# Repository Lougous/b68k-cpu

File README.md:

# Overview

This is a single board computer based on Motorola 68000. It features:
* 512kiB to 8MiB DRAM (SIMM 30 pins x2)
* basic memory protection / paging
* 8bits expansion bus with 4 slots
* PS/2 keyboard and mouse support
* serial link (TTL)
* boot with serial bootstrap or user flash

Some pictures [here](/doc).

The block diagram below depicts the board architecture:

## Board glue logic

Most board glue logic is implemented with an Altera EPM7128S CPLD. This part is obsolete but modern replacement exists with ~~Actel~~ ~~Microsemi~~ Microchip ATF1508AS (never tested though). The CPLD implements:
* DRAM address multiplexing
* DRAM refresh
* basic memory management: base address translation and inbound check with power of two alignment constraints
* 8-bits expansion bus access, for 8-bits wide or 16-bits wide memory cycle from the 68000
* first stage boot procedure, by copying during reset the 512 first bytes from the flash memory (see MFP chip description below) at address 000000h in DRAM. 

Expansion bus also uses a few discrete logic (74245 buffers and 74138 address decoder).

An additional 74148 encodes interrupt sources to CPU IPL0/1/2.

### memory management

The CPLD provides very basic memory management capabilities, for user mode accesses only (FC2 set to 0). It relies on two value set with four registers. These registers are write only, 16-bits, but only the upper bit 15:8 are used.

| register    | address | description             |
|:-----------:|:-------:|:------------------------|
| MMU_BASE_LO | FE0000h | base address bits 19:12 |
| MMU_BASE_HI | FE0002h | base address bits 22:20 |
| MMU_MASK_LO | FE0004h | address mask bits 19:12 |
| MMU_MASK_HI | FE0006h | address mask bits 21:20 |

Any user address is and'ed with MMU_MASK then or'ed with MMU_BASE. It results in a memory area allocated to a user program with a power of two size, with a base address aligned to its own size. Any user access that targets an address above the allocated size ends with a bus error.

### interrupt management

The autovectored interrupt scheme is used (VPA# assertion). To save pins on the CPLD the FC0 and FC1 are not available to identify an interrupt acknowledge cycle, so any read cycle at FFFFFFh with FC2 set to 1 is considered as such.

### 8-bits expansion bus

This bus provides access to 5 peripherals:
* 4 available through dedicated connectors (2x10 female pin headers)
* 1 embeded to the board: the MFP

It provides for each peripheral up to 128kiB aperture into CPU memory space.

The table below lists the signals on this bus as seen for each slot.

| signal  | type              | shared  | description          |
|:-------:|:-----------------:|:-------:|:--------------------:|
| RST#    | input             | yes     | system reset         |
| CE#     | input             | no      | access enable        |
| ACK#    | open drain output | yes     | access acknowledge   |
| WE#     | input             | yes     | write enable         |
| ALE#    | input             | yes     | address latch enable |
| IRQ#    | open drain output | option  | interrupt request    |
| A0      | input             | yes     | address bit 0        |
| AD[7:0] | bidir             | yes     | address / data       |

#### single access cycles

This is how translates a byte access from the 68000 (UDS# or LDS# alone)

note: peripherals like the MFP ignore the address bits 16:1 and can ignore the ALE# signal.

#### multiple access cycles

This is how translates a 16-bits access from the 68000 (UDS# and LDS#)

### Bootstrap loading

Right after a reset, the CPLD starts by transfering 512 bytes of data from the MFP FLASH_DATA register into the first bytes of DRAM. Then the very first 68000 memory access (at 0000000h) is performed.

Because any software is to be much bigger than just 512-bytes, this chunk of code must itself include assembly instructions to copy the rest of the code - still accessing FLASH_DATA register.

The MFP contains two software images for the 68000:
* a serial bootstrap, loading from the serial interface the binary to jump in, that is enables by pressing 's' key on a keyboard plugged into the PS/2 port
* or an embedded binary to jump in.

To change the embedded binary, the MFP firmware must be recompiled and programmed (the 68000 binary is a constant data table within the microcontroller firmware).

## MFP (multifunction peripheral)

This is a software defined chip base on a PIC18F27K42 microcontroller. It provides:
* embedded flash with 2 software images for the 68000, selection by detecting pressed key at reset. 
* IOs/timer with dedicated low-priority interrupt: two PS/2 port, one serial link, 1 kHz RTC timer
* 250 Hz system timer with dedicated highest-priority interrupt
* hard/soft reset
* debug register (POST or so)

The MFP has only two memory locations accessible through the expansion bus: one to set the actual register to access, the other to read or write data from/to the register.

| register    | address | description             |
|:-----------:|:-------:|:------------------------|
| MFP_DATA    | F00000h | MFP register data |
| MFP_ADDRESS | F00001h | MFP register index |

### Register set

| register    | index   | description             |
|:-----------:|:-------:|:------------------------|
| FLASH_DATA  | 0       | boot flash data access. flash data pointer auto increments |
| TICKS       | 3       | 4-us ticks counter, 0-249 |
| UART_STS    | 4       | UART status<br>bit 7: TX ready<br>bit 1: RX FIFO overflow<br>bit 0: RX FIFO underflow |
| UART_DATA   | 5       | UART data in/out |
| POST        | 7       | POST code (debug) |
| PS2P0_STS   | 8       | PS/2 port 0 status<br>bit 0: data available |
| PS2P0_DATA  | 9       | PS/2 port 0 data |
| PS2P1_STS   | 10      | PS/2 port 1 status<br>bit 0: data available |
| PS2P1_DATA  | 11      | PS/2 port 1 data |
| SYSCFG      | 12      | system tick configuration<br>bit 0: enable timer interrupt<br>bit 5: set by bootstap loader to prevent flash to RAM boot transfer<br>bit 6: enable self immediate interrupt<br>bit 7: soft reset |
| SYSSTS      | 13      |  system tick status<br>bit 0: timer interrupt pending<br>bit 6: self immediate interrupt pending |
| IRQCFG      | 14      | interrupt controller configuration<br>bit 0: enable RTC interrupt<br>bit 1: enable PS/2 keyboard interrupt<br>bit 2: enable PS/2 mouse interrupt<br>bit 3: enable UART RX interrupt |
| IRQSTS      | 15      | interrupt controller status<br>bit 0: RTC interrupt pending<br>bit 1: PS/2 keyboard interrupt pending<br>bit 2: PS/2 mouse interrupt pending<br>bit 3: UART RX interrupt pending |

# Memory mapping

| memory range      | access | size   | memory area
|:-----------------:|:------:|:------:|:-----
| 000000h - 7FFFFFh | U/S    | 8MiB   | DRAM. memory address translation/mask/check for user mode only |
| 800000h - EFFFFFh | S	     | 7MiB   | DO NOT USE. mirrors F00000h - FFFFFFh                          |
| F00000h - F1FFFFh | S      | 128kiB | MFP registers. address bits 16:1 are ignored                   |
| F20000h - F3FFFFh | S      | 128kiB | expansion bus connector J9                                     |
| F40000h - F5FFFFh | S      | 128kiB | expansion bus connector J11                                    |
| F60000h - F7FFFFh | S      | 128kiB | DO NOT USE. reserved for expansion bus hardware implementation |
| F80000h - F9FFFFh | U*/S   | 128kiB | expansion bus connector J10. *: user access to be removed      |
| FA0000h - FBFFFFh | S      | 128kiB | DO NOT USE. unmapped, might be used for another peripheral slot |
| FC0000h - FDFFFFh | S      | 128kiB | expansion bus connector J8                                     |
| FE0000h - FFFFFFh | S      | 128kiB | restricted to PMMU register configuration                      |

# BOM

This table below is no spec, it just shows the parts that equip the board on my desk.

| Reference  | Part |
|:-----------------:|:------:|
| RN1 | not populated |
| U1 | MC68HC000FN20 |
| U2 | 74F138 |
| U3, U6, U7 | 74F245 |
| U4 | EPM7128SLC84-10 |
| U5 | PIC18F27K42SP |
| U8 | 74HC148 |
| X2 | 12-MHz |

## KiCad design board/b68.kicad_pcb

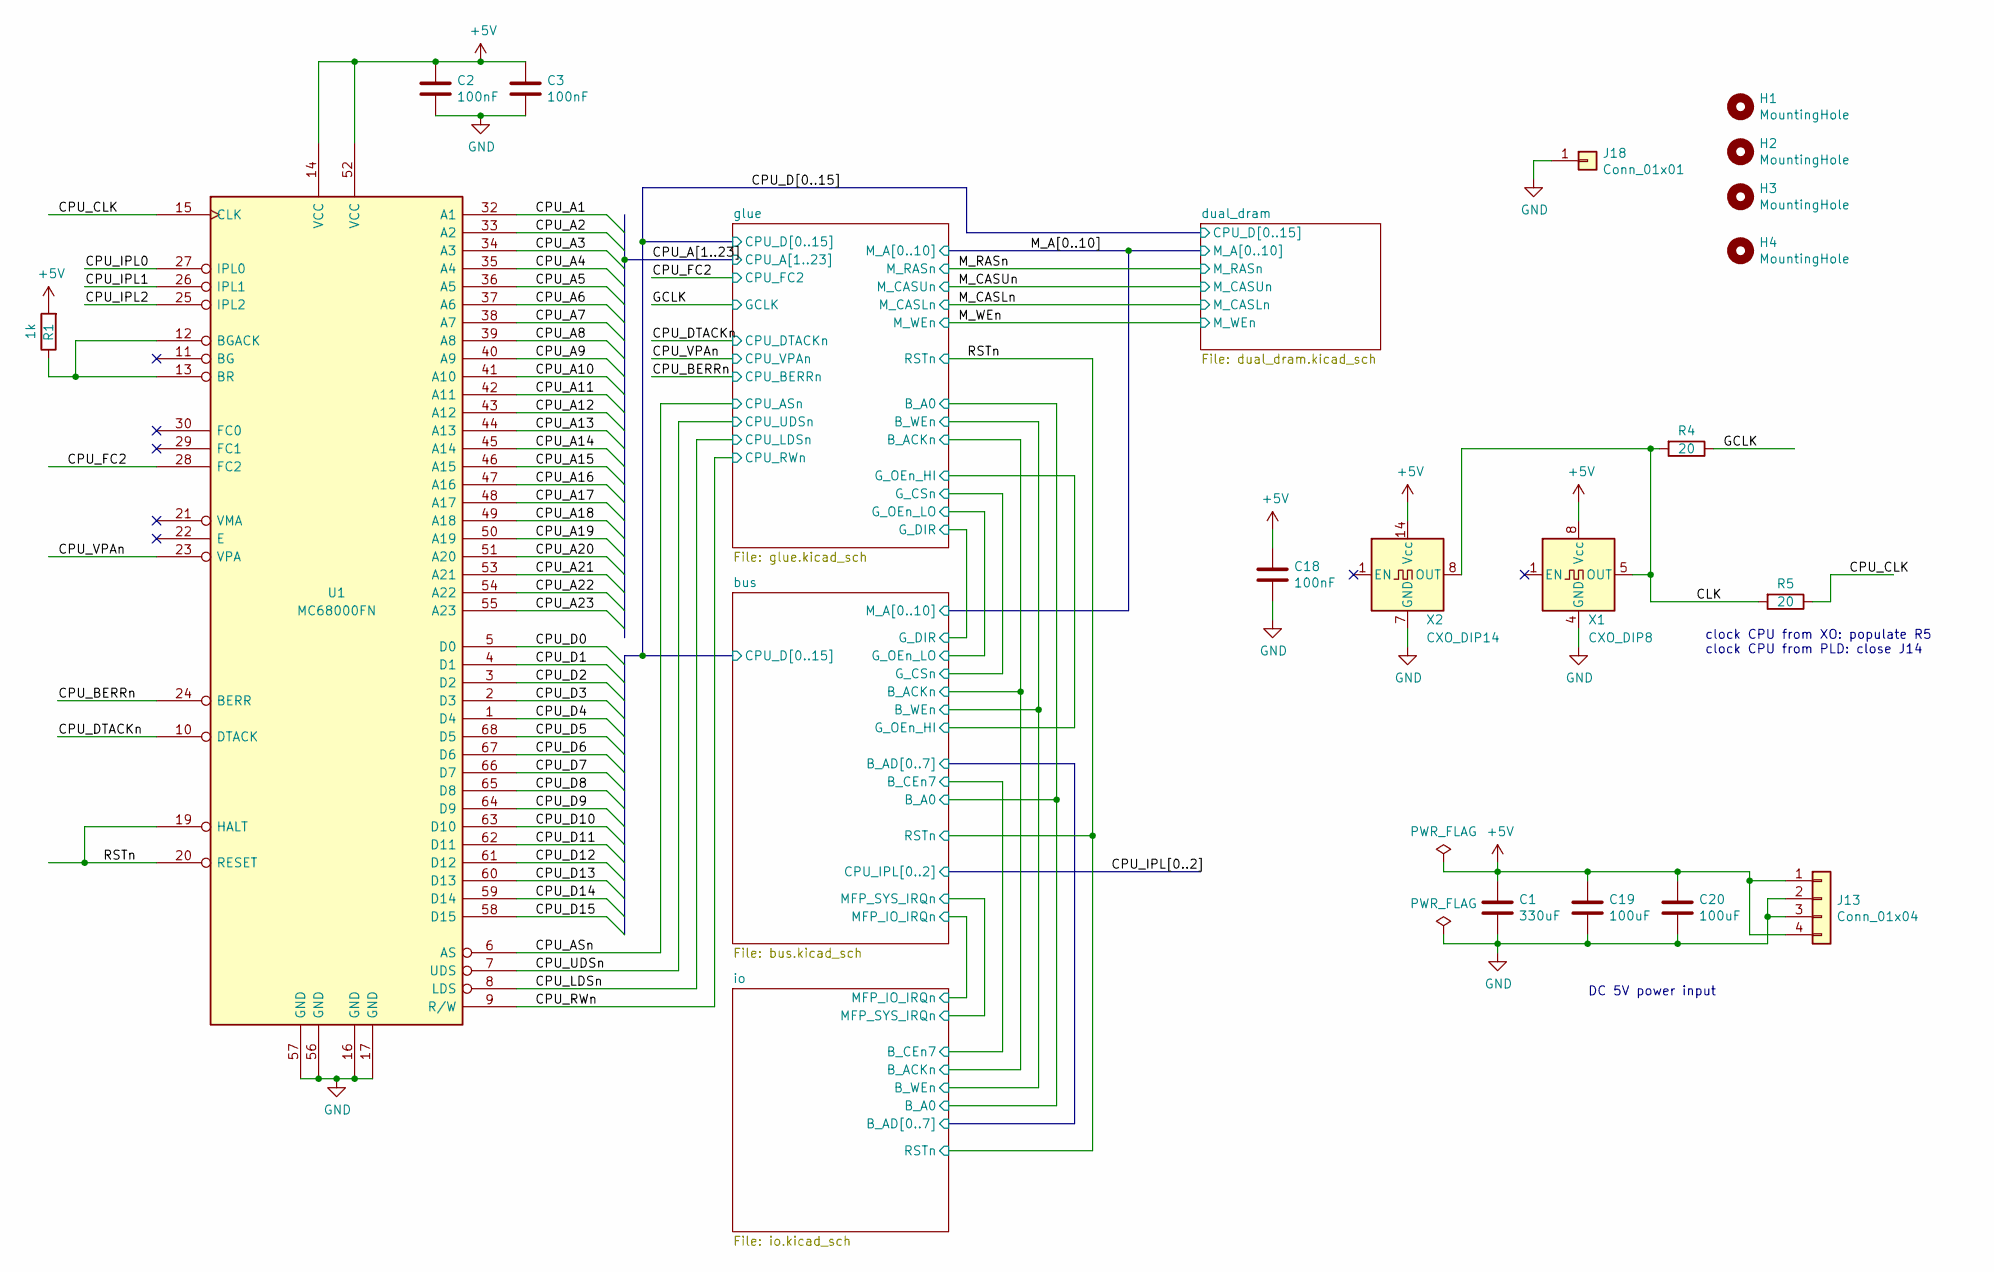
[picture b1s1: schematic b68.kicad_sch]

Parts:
C1: 330uF; CP_Radial_D8.0mm_P3.50mm
C2, C3, C18: 100nF; C_Disc_D4.3mm_W1.9mm_P5.00mm
C19, C20: 100uF; CP_Radial_D5.0mm_P2.50mm
H1, H2, H3, H4: MountingHole; MountingHole_2.7mm_M2.5_DIN965_Pad
J13: Conn_01x04; PinHeader_1x04_P2.54mm_Vertical
J18: Conn_01x01; PinHeader_1x01_P2.54mm_Vertical
R1: 1k; R_Axial_DIN0204_L3.6mm_D1.6mm_P7.62mm_Horizontal
R4, R5: 20; R_Axial_DIN0204_L3.6mm_D1.6mm_P7.62mm_Horizontal
U1: MC68000FN; PLCC-68_THT-Socket
X1: CXO_DIP8; Oscillator_DIP-8
X2: CXO_DIP14; Oscillator_DIP-14

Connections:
+5V: C1.1, C2.1, C3.1, C18.1, C19.1, C20.1, J13.1, J13.4, R1.2, U1.14 (VCC), U1.52 (VCC), X1.8 (Vcc), X2.14 (Vcc); also elsewhere on the board
/CLK: R4.2, R5.2, X1.5 (OUT), X2.8 (OUT)
/CPU_A1: U1.32 (A1); also elsewhere on the board
/CPU_A2: U1.33 (A2); also elsewhere on the board
/CPU_A3: U1.34 (A3); also elsewhere on the board
/CPU_A4: U1.35 (A4); also elsewhere on the board
/CPU_A5: U1.36 (A5); also elsewhere on the board
/CPU_A6: U1.37 (A6); also elsewhere on the board
/CPU_A7: U1.38 (A7); also elsewhere on the board
/CPU_A8: U1.39 (A8); also elsewhere on the board
/CPU_A9: U1.40 (A9); also elsewhere on the board
/CPU_A10: U1.41 (A10); also elsewhere on the board
/CPU_A11: U1.42 (A11); also elsewhere on the board
/CPU_A12: U1.43 (A12); also elsewhere on the board
/CPU_A13: U1.44 (A13); also elsewhere on the board
/CPU_A14: U1.45 (A14); also elsewhere on the board
/CPU_A15: U1.46 (A15); also elsewhere on the board
/CPU_A16: U1.47 (A16); also elsewhere on the board
/CPU_A17: U1.48 (A17); also elsewhere on the board
/CPU_A18: U1.49 (A18); also elsewhere on the board
/CPU_A19: U1.50 (A19); also elsewhere on the board
/CPU_A20: U1.51 (A20); also elsewhere on the board
/CPU_A21: U1.53 (A21); also elsewhere on the board
/CPU_A22: U1.54 (A22); also elsewhere on the board
/CPU_A23: U1.55 (A23); also elsewhere on the board
/CPU_ASn: U1.6 (AS); also elsewhere on the board
/CPU_BERRn: U1.24 (BERR); also elsewhere on the board
/CPU_CLK: R5.1, U1.15 (CLK)
/CPU_D0: U1.5 (D0); also elsewhere on the board
/CPU_D1: U1.4 (D1); also elsewhere on the board
/CPU_D2: U1.3 (D2); also elsewhere on the board
/CPU_D3: U1.2 (D3); also elsewhere on the board
/CPU_D4: U1.1 (D4); also elsewhere on the board
/CPU_D5: U1.68 (D5); also elsewhere on the board
/CPU_D6: U1.67 (D6); also elsewhere on the board
/CPU_D7: U1.66 (D7); also elsewhere on the board
/CPU_D8: U1.65 (D8); also elsewhere on the board
/CPU_D9: U1.64 (D9); also elsewhere on the board
/CPU_D10: U1.63 (D10); also elsewhere on the board
/CPU_D11: U1.62 (D11); also elsewhere on the board
/CPU_D12: U1.61 (D12); also elsewhere on the board
/CPU_D13: U1.60 (D13); also elsewhere on the board
/CPU_D14: U1.59 (D14); also elsewhere on the board
/CPU_D15: U1.58 (D15); also elsewhere on the board
/CPU_DTACKn: U1.10 (DTACK); also elsewhere on the board
/CPU_FC2: U1.28 (FC2); also elsewhere on the board
/CPU_IPL0: U1.27 (IPL0); also elsewhere on the board
/CPU_IPL1: U1.26 (IPL1); also elsewhere on the board
/CPU_IPL2: U1.25 (IPL2); also elsewhere on the board
/CPU_LDSn: U1.8 (LDS); also elsewhere on the board
/CPU_RWn: U1.9 (R/W); also elsewhere on the board
/CPU_UDSn: U1.7 (UDS); also elsewhere on the board
/CPU_VPAn: U1.23 (VPA); also elsewhere on the board
/GCLK: R4.1; also elsewhere on the board
/RSTn: U1.19 (HALT), U1.20 (RESET); also elsewhere on the board
GND: C1.2, C2.2, C3.2, C18.2, C19.2, C20.2, J13.2, J13.3, J18.1, U1.16 (GND), U1.17 (GND), U1.56 (GND), U1.57 (GND), X1.4 (GND), X2.7 (GND); also elsewhere on the board
unnamed: R1.1, U1.12 (BGACK), U1.13 (BR)

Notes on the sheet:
clock CPU from XO: populate R5 clock CPU from PLD: close J14
DC 5V power input

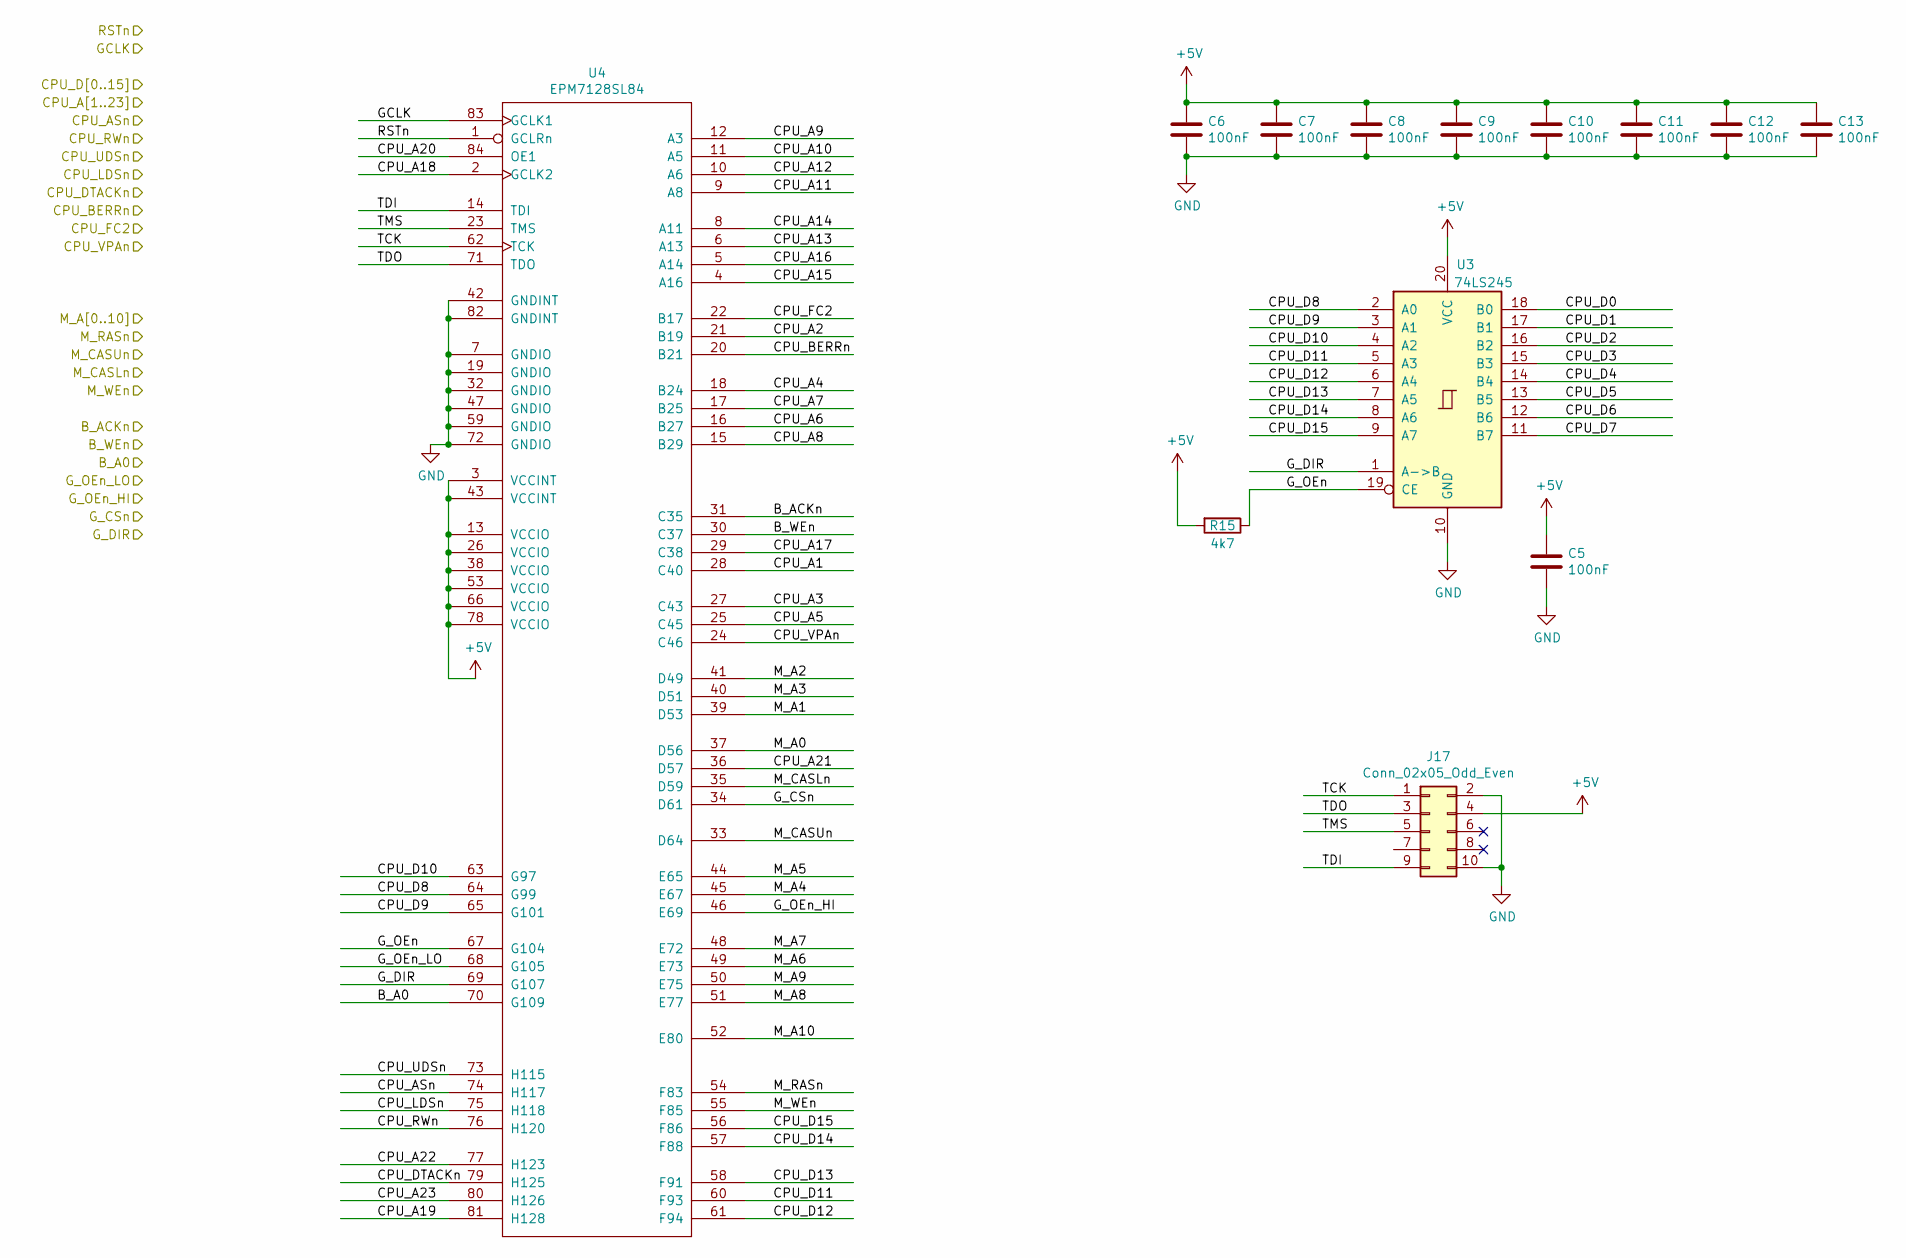
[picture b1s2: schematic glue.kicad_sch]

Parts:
C5, C6, C7, C8, C9, C10, C11, C12, C13: 100nF; C_Disc_D4.3mm_W1.9mm_P5.00mm
J17: Conn_02x05_Odd_Even; PinHeader_2x05_P2.54mm_Vertical
R15: 4k7; R_Axial_DIN0204_L3.6mm_D1.6mm_P2.54mm_Vertical
U3: 74LS245; DIP-20_W7.62mm_Socket
U4: EPM7128SL84; PLCC-84_THT-Socket

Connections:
+5V: C5.1, C6.1, C7.1, C8.1, C9.1, C10.1, C11.1, C12.1, C13.1, J17.4, R15.2, U3.20 (VCC), U4.3 (VCCINT), U4.13 (VCCIO), U4.26 (VCCIO), U4.38 (VCCIO), U4.43 (VCCINT), U4.53 (VCCIO), U4.66 (VCCIO), U4.78 (VCCIO); also elsewhere on the board
/CPU_A1: U4.28 (C40); also elsewhere on the board
/CPU_A2: U4.21 (B19); also elsewhere on the board
/CPU_A3: U4.27 (C43); also elsewhere on the board
/CPU_A4: U4.18 (B24); also elsewhere on the board
/CPU_A5: U4.25 (C45); also elsewhere on the board
/CPU_A6: U4.16 (B27); also elsewhere on the board
/CPU_A7: U4.17 (B25); also elsewhere on the board
/CPU_A8: U4.15 (B29); also elsewhere on the board
/CPU_A9: U4.12 (A3); also elsewhere on the board
/CPU_A10: U4.11 (A5); also elsewhere on the board
/CPU_A11: U4.9 (A8); also elsewhere on the board
/CPU_A12: U4.10 (A6); also elsewhere on the board
/CPU_A13: U4.6 (A13); also elsewhere on the board
/CPU_A14: U4.8 (A11); also elsewhere on the board
/CPU_A15: U4.4 (A16); also elsewhere on the board
/CPU_A16: U4.5 (A14); also elsewhere on the board
/CPU_A17: U4.29 (C38); also elsewhere on the board
/CPU_A18: U4.2 (GCLK2); also elsewhere on the board
/CPU_A19: U4.81 (H128); also elsewhere on the board
/CPU_A20: U4.84 (OE1); also elsewhere on the board
/CPU_A21: U4.36 (D57); also elsewhere on the board
/CPU_A22: U4.77 (H123); also elsewhere on the board
/CPU_A23: U4.80 (H126); also elsewhere on the board
/CPU_ASn: U4.74 (H117); also elsewhere on the board
/CPU_BERRn: U4.20 (B21); also elsewhere on the board
/CPU_D0: U3.18 (B0); also elsewhere on the board
/CPU_D1: U3.17 (B1); also elsewhere on the board
/CPU_D2: U3.16 (B2); also elsewhere on the board
/CPU_D3: U3.15 (B3); also elsewhere on the board
/CPU_D4: U3.14 (B4); also elsewhere on the board
/CPU_D5: U3.13 (B5); also elsewhere on the board
/CPU_D6: U3.12 (B6); also elsewhere on the board
/CPU_D7: U3.11 (B7); also elsewhere on the board
/CPU_D8: U3.2 (A0), U4.64 (G99); also elsewhere on the board
/CPU_D9: U3.3 (A1), U4.65 (G101); also elsewhere on the board
/CPU_D10: U3.4 (A2), U4.63 (G97); also elsewhere on the board
/CPU_D11: U3.5 (A3), U4.60 (F93); also elsewhere on the board
/CPU_D12: U3.6 (A4), U4.61 (F94); also elsewhere on the board
/CPU_D13: U3.7 (A5), U4.58 (F91); also elsewhere on the board
/CPU_D14: U3.8 (A6), U4.57 (F88); also elsewhere on the board
/CPU_D15: U3.9 (A7), U4.56 (F86); also elsewhere on the board
/CPU_DTACKn: U4.79 (H125); also elsewhere on the board
/CPU_FC2: U4.22 (B17); also elsewhere on the board
/CPU_LDSn: U4.75 (H118); also elsewhere on the board
/CPU_RWn: U4.76 (H120); also elsewhere on the board
/CPU_UDSn: U4.73 (H115); also elsewhere on the board
/CPU_VPAn: U4.24 (C46); also elsewhere on the board
/GCLK: U4.83 (GCLK1); also elsewhere on the board
/M_A0: U4.37 (D56); also elsewhere on the board
/M_A1: U4.39 (D53); also elsewhere on the board
/M_A2: U4.41 (D49); also elsewhere on the board
/M_A3: U4.40 (D51); also elsewhere on the board
/M_A4: U4.45 (E67); also elsewhere on the board
/M_A5: U4.44 (E65); also elsewhere on the board
/M_A6: U4.49 (E73); also elsewhere on the board
/M_A7: U4.48 (E72); also elsewhere on the board
/M_A8: U4.51 (E77); also elsewhere on the board
/M_A9: U4.50 (E75); also elsewhere on the board
/M_A10: U4.52 (E80); also elsewhere on the board
/M_CASLn: U4.35 (D59); also elsewhere on the board
/M_CASUn: U4.33 (D64); also elsewhere on the board
/M_RASn: U4.54 (F83); also elsewhere on the board
/M_WEn: U4.55 (F85); also elsewhere on the board
/RSTn: U4.1 (GCLRn); also elsewhere on the board
/bus/B_ACKn: U4.31 (C35); also elsewhere on the board
/bus/B_DIR: U3.1 (A->B), U4.69 (G107); also elsewhere on the board
/bus/B_WEn: U4.30 (C37); also elsewhere on the board
/glue/B_A0: U4.70 (G109); also elsewhere on the board
/glue/G_CSn: U4.34 (D61); also elsewhere on the board
/glue/G_OEn: R15.1, U3.19 (CE), U4.67 (G104)
/glue/G_OEn_HI: U4.46 (E69); also elsewhere on the board
/glue/G_OEn_LO: U4.68 (G105); also elsewhere on the board
/glue/TCK: J17.1, U4.62 (TCK)
/glue/TDI: J17.9, U4.14 (TDI)
/glue/TDO: J17.3, U4.71 (TDO)
/glue/TMS: J17.5, U4.23 (TMS)
GND: C5.2, C6.2, C7.2, C8.2, C9.2, C10.2, C11.2, C12.2, C13.2, J17.2, J17.10, U3.10 (GND), U4.7 (GNDIO), U4.19 (GNDIO), U4.32 (GNDIO), U4.42 (GNDINT), U4.47 (GNDIO), U4.59 (GNDIO), U4.72 (GNDIO), U4.82 (GNDINT); also elsewhere on the board

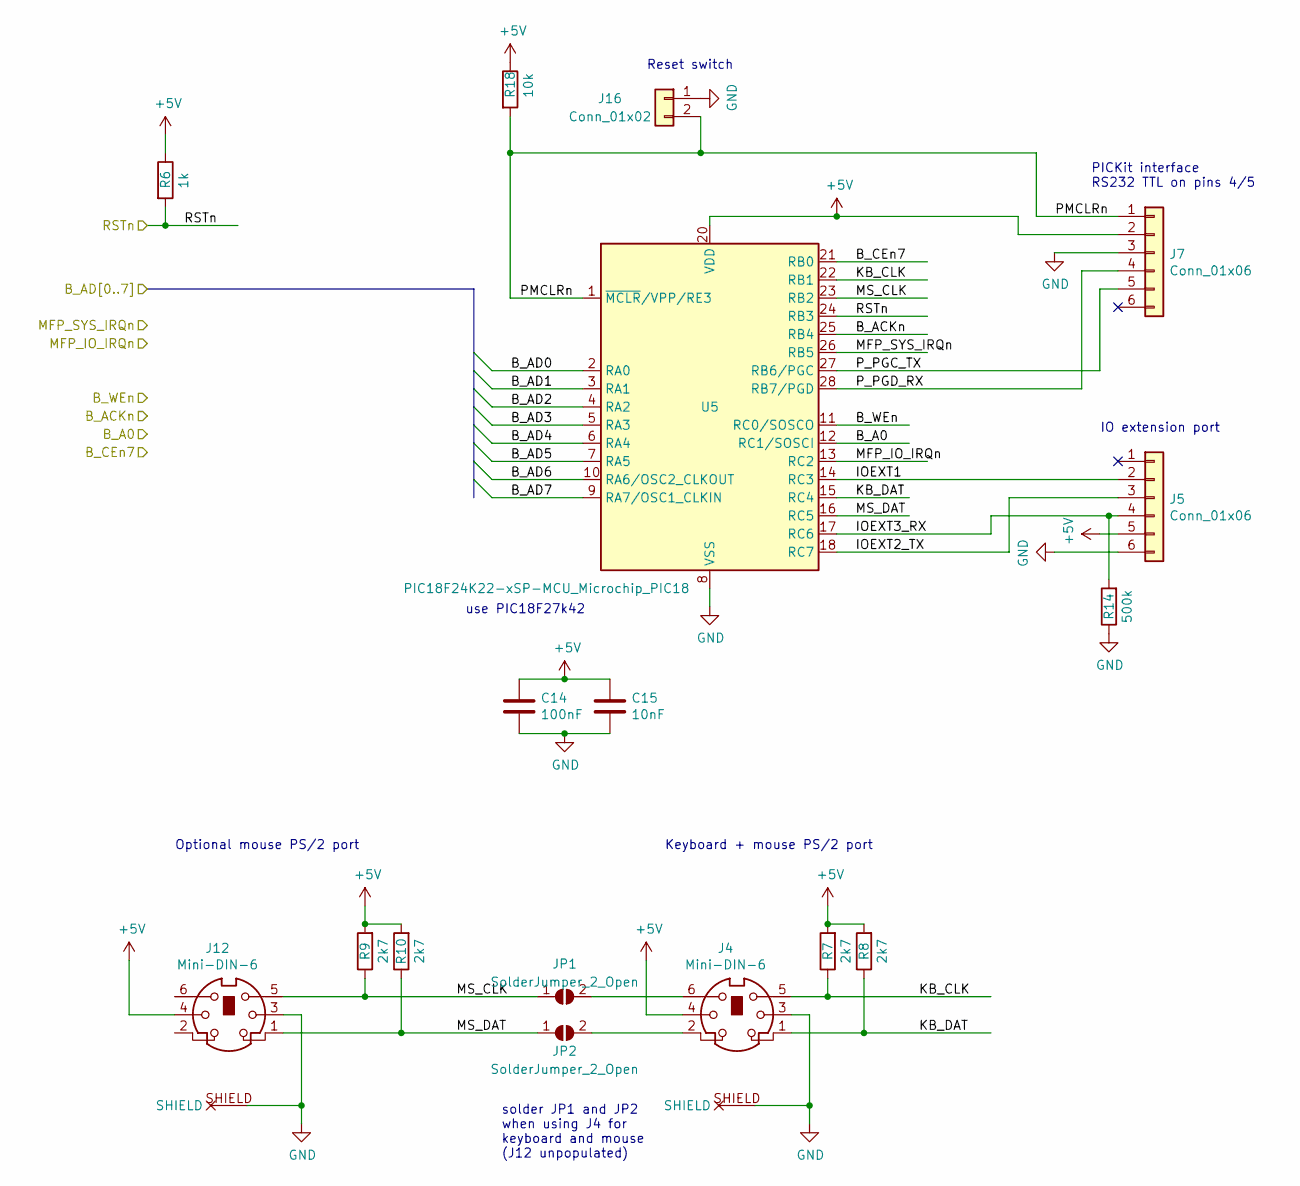
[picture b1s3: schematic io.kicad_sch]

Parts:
C14: 100nF; C_Disc_D4.3mm_W1.9mm_P5.00mm
C15: 10nF; C_Disc_D4.3mm_W1.9mm_P5.00mm
J4, J12: Mini-DIN-6; mini-DIN_6_PS2
J5, J7: Conn_01x06; PinHeader_1x06_P2.54mm_Vertical
J16: Conn_01x02; PinHeader_1x02_P2.54mm_Vertical
JP1, JP2: SolderJumper_2_Open; SolderJumper-2_P1.3mm_Open_RoundedPad1.0x1.5mm
R6: 1k; R_Axial_DIN0204_L3.6mm_D1.6mm_P7.62mm_Horizontal
R7, R8, R9, R10: 2k7; R_Axial_DIN0204_L3.6mm_D1.6mm_P2.54mm_Vertical
R14: 500k; R_Axial_DIN0204_L3.6mm_D1.6mm_P7.62mm_Horizontal
R18: 10k; R_Axial_DIN0204_L3.6mm_D1.6mm_P7.62mm_Horizontal
U5: PIC18F24K22-xSP-MCU_Microchip_PIC18; DIP-28_W7.62mm_Socket

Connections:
+5V: C14.1, C15.1, J4.4, J5.5, J7.2, J12.4, R6.1, R7.2, R8.2, R9.2, R10.2, R18.1, U5.20 (VDD); also elsewhere on the board
/RSTn: R6.2, U5.24 (RB3); also elsewhere on the board
/bus/B_ACKn: U5.25 (RB4); also elsewhere on the board
/bus/B_AD0: U5.2 (RA0); also elsewhere on the board
/bus/B_AD1: U5.3 (RA1); also elsewhere on the board
/bus/B_AD2: U5.4 (RA2); also elsewhere on the board
/bus/B_AD3: U5.5 (RA3); also elsewhere on the board
/bus/B_AD4: U5.6 (RA4); also elsewhere on the board
/bus/B_AD5: U5.7 (RA5); also elsewhere on the board
/bus/B_AD6: U5.10 (RA6/OSC2_CLKOUT); also elsewhere on the board
/bus/B_AD7: U5.9 (RA7/OSC1_CLKIN); also elsewhere on the board
/bus/B_CEn7: U5.21 (RB0); also elsewhere on the board
/bus/B_IRQ0n: U5.13 (RC2); also elsewhere on the board
/bus/B_WEn: U5.11 (RC0/SOSCO); also elsewhere on the board
/glue/B_A0: U5.12 (RC1/SOSCI); also elsewhere on the board
/io/IOEXT1: J5.2, U5.14 (RC3)
/io/IOEXT2_TX: J5.3, U5.18 (RC7)
/io/IOEXT3_RX: J5.4, R14.2, U5.17 (RC6)
/io/KB_CLK: J4.5, R7.1, U5.22 (RB1)
/io/KB_DAT: J4.1, R8.1, U5.15 (RC4)
/io/MFP_SYS_IRQn: U5.26 (RB5); also elsewhere on the board
/io/MS_CLK: J12.5, JP1.1 (A), R9.1, U5.23 (RB2)
/io/MS_DAT: J12.1, JP2.1 (A), R10.1, U5.16 (RC5)
/io/PMCLRn: J7.1, J16.2, R18.2, U5.1 (~MCLR/VPP/RE3)
/io/P_PGC_TX: J7.5, U5.27 (RB6/PGC)
/io/P_PGD_RX: J7.4, U5.28 (RB7/PGD)
GND: C14.2, C15.2, J4.3, J4.SHIELD, J5.6, J7.3, J12.3, J12.SHIELD, J16.1, R14.1, U5.8 (VSS), U5.19 (VSS); also elsewhere on the board
unnamed: J4.2, JP2.2 (B)
unnamed: J4.6, JP1.2 (B)

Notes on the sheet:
use PIC18F27k42
Optional mouse PS/2 port
IO extension port
Reset switch
solder JP1 and JP2 when using J4 for keyboard and mouse (J12 unpopulated)
PICKit interface RS232 TTL on pins 4/5
Keyboard + mouse PS/2 port

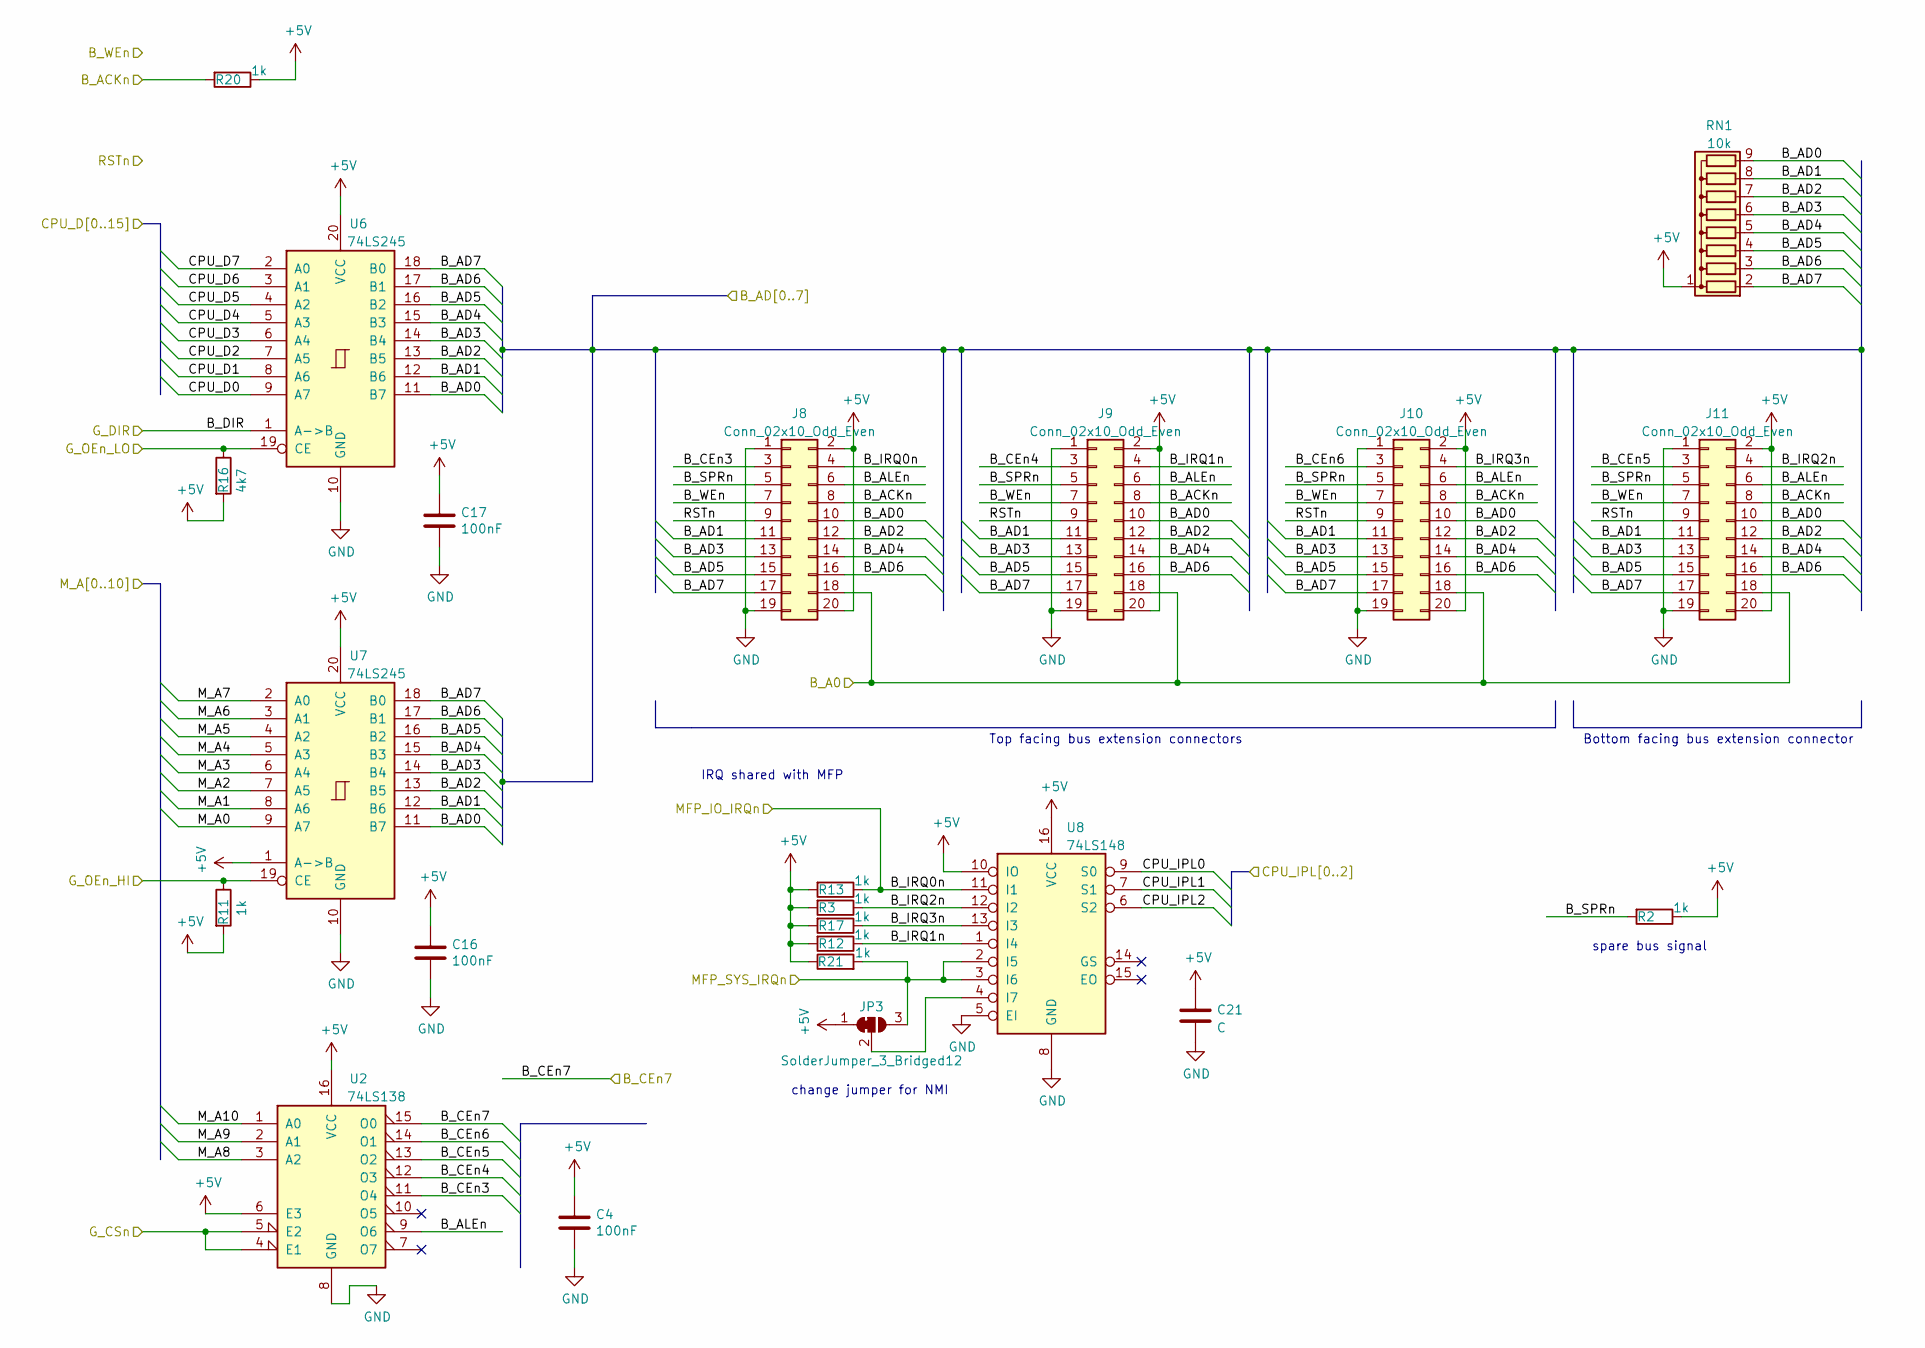
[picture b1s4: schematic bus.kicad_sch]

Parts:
C4, C16, C17: 100nF; C_Disc_D4.3mm_W1.9mm_P5.00mm
C21: C; C_Disc_D4.3mm_W1.9mm_P5.00mm
J8, J9, J10, J11: Conn_02x10_Odd_Even; PinSocket_2x10_P2.54mm_Vertical
JP3: SolderJumper_3_Bridged12; SolderJumper-3_P1.3mm_Bridged12_RoundedPad1.0x1.5mm_NumberL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
R2, R3, R12, R13, R17, R20, R21: 1k; R_Axial_DIN0204_L3.6mm_D1.6mm_P7.62mm_Horizontal
R11: 1k; R_Axial_DIN0204_L3.6mm_D1.6mm_P2.54mm_Vertical
R16: 4k7; R_Axial_DIN0204_L3.6mm_D1.6mm_P2.54mm_Vertical
RN1: 10k; R_Array_SIP9
U2: 74LS138; DIP-16_W7.62mm_Socket
U6, U7: 74LS245; DIP-20_W7.62mm_Socket
U8: 74LS148; DIP-16_W7.62mm_Socket

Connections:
+5V: C4.1, C16.1, C17.1, C21.1, J8.2, J8.20, J9.2, J9.20, J10.2, J10.20, J11.2, J11.20, JP3.1 (A), R2.1, R3.2, R11.2, R12.2, R13.2, R16.2, R17.2, R20.1, R21.1, RN1.1 (common), U2.6 (E3), U2.16 (VCC), U6.20 (VCC), U7.1 (A->B), U7.20 (VCC), U8.10 (IO), U8.16 (VCC); also elsewhere on the board
/CPU_D0: U6.9 (A7); also elsewhere on the board
/CPU_D1: U6.8 (A6); also elsewhere on the board
/CPU_D2: U6.7 (A5); also elsewhere on the board
/CPU_D3: U6.6 (A4); also elsewhere on the board
/CPU_D4: U6.5 (A3); also elsewhere on the board
/CPU_D5: U6.4 (A2); also elsewhere on the board
/CPU_D6: U6.3 (A1); also elsewhere on the board
/CPU_D7: U6.2 (A0); also elsewhere on the board
/CPU_IPL0: U8.9 (S0); also elsewhere on the board
/CPU_IPL1: U8.7 (S1); also elsewhere on the board
/CPU_IPL2: U8.6 (S2); also elsewhere on the board
/M_A0: U7.9 (A7); also elsewhere on the board
/M_A1: U7.8 (A6); also elsewhere on the board
/M_A2: U7.7 (A5); also elsewhere on the board
/M_A3: U7.6 (A4); also elsewhere on the board
/M_A4: U7.5 (A3); also elsewhere on the board
/M_A5: U7.4 (A2); also elsewhere on the board
/M_A6: U7.3 (A1); also elsewhere on the board
/M_A7: U7.2 (A0); also elsewhere on the board
/M_A8: U2.3 (A2); also elsewhere on the board
/M_A9: U2.2 (A1); also elsewhere on the board
/M_A10: U2.1 (A0); also elsewhere on the board
/RSTn: J8.9, J9.9, J10.9, J11.9; also elsewhere on the board
/bus/B_ACKn: J8.8, J9.8, J10.8, J11.8, R20.2; also elsewhere on the board
/bus/B_AD0: J8.10, J9.10, J10.10, J11.10, RN1.9 (R8), U6.11 (B7), U7.11 (B7); also elsewhere on the board
/bus/B_AD1: J8.11, J9.11, J10.11, J11.11, RN1.8 (R7), U6.12 (B6), U7.12 (B6); also elsewhere on the board
/bus/B_AD2: J8.12, J9.12, J10.12, J11.12, RN1.7 (R6), U6.13 (B5), U7.13 (B5); also elsewhere on the board
/bus/B_AD3: J8.13, J9.13, J10.13, J11.13, RN1.6 (R5), U6.14 (B4), U7.14 (B4); also elsewhere on the board
/bus/B_AD4: J8.14, J9.14, J10.14, J11.14, RN1.5 (R4), U6.15 (B3), U7.15 (B3); also elsewhere on the board
/bus/B_AD5: J8.15, J9.15, J10.15, J11.15, RN1.4 (R3), U6.16 (B2), U7.16 (B2); also elsewhere on the board
/bus/B_AD6: J8.16, J9.16, J10.16, J11.16, RN1.3 (R2), U6.17 (B1), U7.17 (B1); also elsewhere on the board
/bus/B_AD7: J8.17, J9.17, J10.17, J11.17, RN1.2 (R1), U6.18 (B0), U7.18 (B0); also elsewhere on the board
/bus/B_ALEn: J8.6, J9.6, J10.6, J11.6, U2.9 (O6)
/bus/B_CEn3: J8.3, U2.11 (O4)
/bus/B_CEn4: J9.3, U2.12 (O3)
/bus/B_CEn5: J11.3, U2.13 (O2)
/bus/B_CEn6: J10.3, U2.14 (O1)
/bus/B_CEn7: U2.15 (O0); also elsewhere on the board
/bus/B_DIR: U6.1 (A->B); also elsewhere on the board
/bus/B_IRQ0n: J8.4, R13.1, U8.11 (I1); also elsewhere on the board
/bus/B_IRQ1n: J9.4, R12.1, U8.1 (I4)
/bus/B_IRQ2n: J11.4, R3.1, U8.12 (I2)
/bus/B_IRQ3n: J10.4, R17.1, U8.13 (I3)
/bus/B_SPRn: J8.5, J9.5, J10.5, J11.5, R2.2
/bus/B_WEn: J8.7, J9.7, J10.7, J11.7; also elsewhere on the board
/glue/B_A0: J8.18, J9.18, J10.18, J11.18; also elsewhere on the board
/glue/G_CSn: U2.4 (E1), U2.5 (E2); also elsewhere on the board
/glue/G_OEn_HI: R11.1, U7.19 (CE); also elsewhere on the board
/glue/G_OEn_LO: R16.1, U6.19 (CE); also elsewhere on the board
/io/MFP_SYS_IRQn: JP3.3 (B), R21.2, U8.2 (I5), U8.3 (I6); also elsewhere on the board
GND: C4.2, C16.2, C17.2, C21.2, J8.1, J8.19, J9.1, J9.19, J10.1, J10.19, J11.1, J11.19, U2.8 (GND), U6.10 (GND), U7.10 (GND), U8.5 (EI), U8.8 (GND); also elsewhere on the board
unnamed: JP3.2 (C), U8.4 (I7)

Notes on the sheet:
Bottom facing bus extension connector
spare bus signal
change jumper for NMI
IRQ shared with MFP
Top facing bus extension connectors

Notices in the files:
board/b68.kicad_pcb:
CPU-68K v2.0b - (C) 2024
